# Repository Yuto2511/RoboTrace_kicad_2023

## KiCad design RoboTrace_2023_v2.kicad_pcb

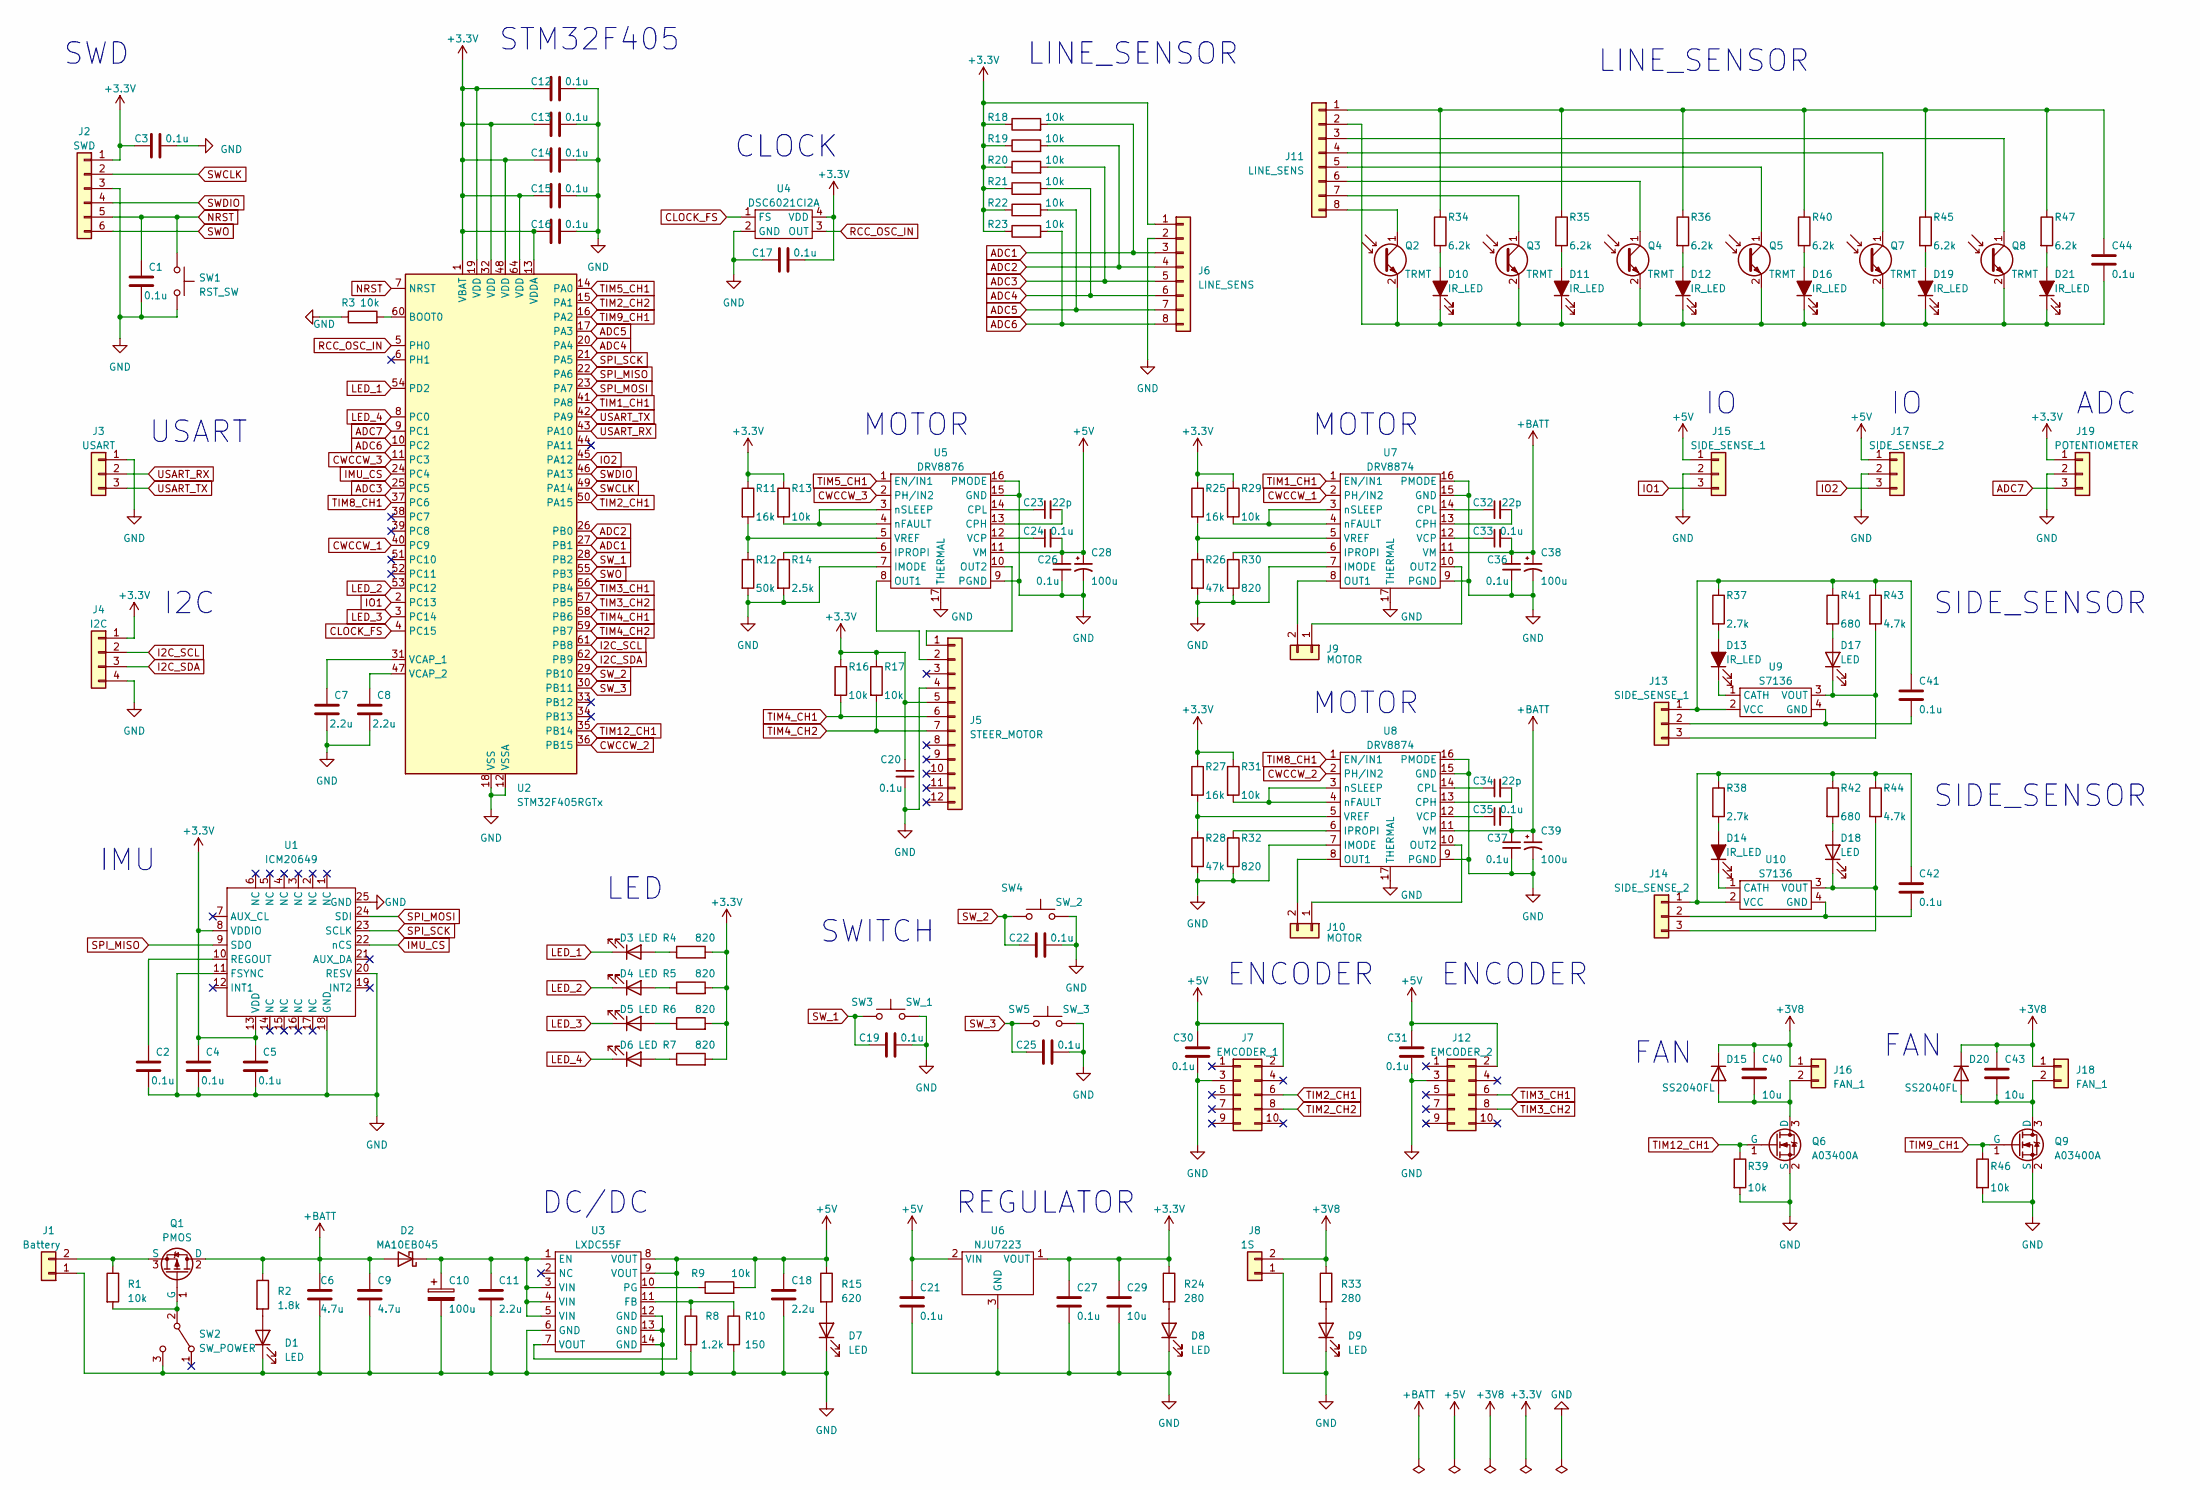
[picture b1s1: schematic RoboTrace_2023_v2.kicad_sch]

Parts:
C1, C2, C3, C4, C5, C12, C13, C14, C15, C16, C17, C19, C20, C21, C22, C24, C25, C26, C27, C30, C31, C33, C35, C36, C37, C41, C42, C44: 0.1u; C_0603_1608Metric
C6, C9: 4.7u; C_1206_3216Metric
C7, C8, C11, C18: 2.2u; C_0603_1608Metric
C10, C28, C38, C39: 100u; CP_EIA-7343-15_Kemet-W
C23, C32, C34: 22p; C_0603_1608Metric
C29, C40, C43: 10u; C_0805_2012Metric
D1, D3, D4, D5, D6, D7, D8, D9, D17, D18: LED; LED_0603_1608Metric
D2: MA10EB045; SO-221BC
D10, D11, D12, D13, D14, D16, D19, D21: IR_LED; LED_0603_1608Metric
D15, D20: SS2040FL; D_SOD-123F
J1: Battery; AMASS_XT30PW-M_1x02_P2.50mm_Horizontal
J2: SWD; JST_SH_BM06B-SRSS-TB_1x06-1MP_P1.00mm_Vertical
J3: USART; JST_SH_BM03B-SRSS-TB_1x03-1MP_P1.00mm_Vertical
J4: I2C; JST_SH_BM04B-SRSS-TB_1x04-1MP_P1.00mm_Vertical
J5: STEER_MOTOR; Molex_200528-0120_1x12-0.5MP_P0.50mm_Horizontal
J6, J11: LINE_SENS; Molex_200528-0080_1x08-0.5MP_P0.50mm_Horizontal
J7: EMCODER_1; PinHeader_2x05_P1.27mm_Vertical
J8: 1S; IL-G_2PIN
J9, J10: MOTOR; JST_PH_B2B-PH-K_1x02_P2.00mm_Vertical
J12: EMCODER_2; PinHeader_2x05_P1.27mm_Vertical
J13, J15: SIDE_SENSE_1; JST_SH_BM03B-SRSS-TB_1x03-1MP_P1.00mm_Vertical
J14, J17: SIDE_SENSE_2; JST_SH_BM03B-SRSS-TB_1x03-1MP_P1.00mm_Vertical
J16, J18: FAN_1; JST_PH_B2B-PH-K_1x02_P2.00mm_Vertical
J19: POTENTIOMETER; JST_SH_BM03B-SRSS-TB_1x03-1MP_P1.00mm_Vertical
Q1: PMOS; TO-252-3_TabPin2
Q2, Q3, Q4, Q5, Q7, Q8: TRMT; LED_0805_2012Metric
Q6, Q9: A03400A; SOT-23
R1, R3, R9, R13, R16, R17, R18, R19, R20, R21, R22, R23, R29, R31, R39, R46: 10k; R_0603_1608Metric
R2: 1.8k; R_0603_1608Metric
R4, R5, R6, R7, R30, R32: 820; R_0603_1608Metric
R8: 1.2k; R_0603_1608Metric
R10: 150; R_0603_1608Metric
R11, R25, R27: 16k; R_0603_1608Metric
R12: 50k; R_0603_1608Metric
R14: 2.5k; R_0603_1608Metric
R15: 620; R_0603_1608Metric
R24, R33: 280; R_0603_1608Metric
R26, R28: 47k; R_0603_1608Metric
R34, R35, R36, R40, R45, R47: 6.2k; R_0603_1608Metric
R37, R38: 2.7k; R_0603_1608Metric
R41, R42: 680; R_0603_1608Metric
R43, R44: 4.7k; R_0603_1608Metric
SW1: RST_SW; SW_SPST_B3U-1000P
SW2: SW_POWER; SSAJ12
SW3: SW_1; SW_SPST_B3U-1000P
SW4: SW_2; SW_SPST_B3U-1000P
SW5: SW_3; SW_SPST_B3U-1000P
U1: ICM20649; QFN-24-1EP_3x3mm_P0.4mm_EP1.75x1.6mm_ThermalVias
U2: STM32F405RGTx; LQFP-64_10x10mm_P0.5mm
U3: LXDC55F; LXDC55FAAA203
U4: DSC6021CI2A
U5: DRV8876; HTSSOP-16-1EP_4.4x5mm_P0.65mm_EP3.4x5mm_Mask2.46x2.31mm_The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
U6: NJU7223; TO-252-2
U7, U8: DRV8874; HTSSOP-16-1EP_4.4x5mm_P0.65mm_EP3.4x5mm_Mask2.46x2.31mm_The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
U9, U10: S7136

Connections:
+3.3V: C3.1, C4.1, C5.1, C12.1, C13.1, C14.1, C15.1, C16.1, C17.2, C20.1, C27.1, C29.1, J2.1, J4.1, J5.5, J6.1, J19.1, R4.2, R5.2, R6.2, R7.2, R11.1, R13.1, R16.1, R17.1, R18.1, R19.1, R20.1, R21.1, R22.1, R23.1, R24.1, R25.1, R27.1, R29.1, R31.1, U1.8 (VDDIO), U1.13 (VDD), U2.1 (VBAT), U2.13 (VDDA), U2.19 (VDD), U2.32 (VDD), U2.48 (VDD), U2.64 (VDD), U4.4 (VDD), U6.1 (VOUT)
+3V8: C40.1, C43.1, D15.1 (K), D20.1 (K), J8.2, J16.1, J18.1, R33.1
+5V: C18.1, C21.1, C24.2, C26.1, C28.1, C30.1, C31.1, J7.2, J12.2, J15.1, J17.1, R9.2, R15.1, U3.7 (VOUT), U3.8 (VOUT), U3.9 (VOUT), U5.11 (VM), U6.2 (VIN)
+BATT: C6.1, C9.1, C33.2, C35.2, C36.1, C37.1, C38.1, C39.1, D2.2 (A), Q1.2 (D), R2.1, U7.11 (VM), U8.11 (VM)
ADC1: J6.3, R18.2, U2.27 (PB1)
ADC2: J6.4, R19.2, U2.26 (PB0)
ADC3: J6.5, R20.2, U2.25 (PC5)
ADC4: J6.6, R21.2, U2.20 (PA4)
ADC5: J6.7, R22.2, U2.17 (PA3)
ADC6: J6.8, R23.2, U2.10 (PC2)
ADC7: J19.3, U2.9 (PC1)
CLOCK_FS: U2.4 (PC15), U4.1 (FS)
CWCCW_1: U2.40 (PC9), U7.2 (PH/IN2)
CWCCW_2: U2.36 (PB15), U8.2 (PH/IN2)
CWCCW_3: U2.11 (PC3), U5.2 (PH/IN2)
GND: C1.2, C2.2, C3.2, C4.2, C5.2, C6.2, C7.2, C8.2, C9.2, C10.2, C11.2, C12.2, C13.2, C14.2, C15.2, C16.2, C17.1, C18.2, C19.2, C20.2, C21.2, C22.2, C25.2, C26.2, C27.2, C28.2, C29.2, C30.2, C31.2, C36.2, C37.2, C38.2, C39.2, D1.1 (K), D7.1 (K), D8.1 (K), D9.1 (K), J1.1, J2.3, J3.1, J4.4, J5.4, J6.2, J7.3, J8.1, J12.3, J15.2, J17.2, J19.2, Q6.2 (S), Q9.2 (S), R3.1, R8.2, R10.2, R12.2, R14.2, R26.2, R28.2, R30.2, R32.2, R39.2, R46.2, SW1.2, SW2.3 (C), SW3.2, SW4.2, SW5.2, U1.11 (FSYNC), U1.18 (GND), U1.20 (RESV), U1.25 (GND), U2.12 (VSSA), U2.18 (VSS), U2.63 (VSS), U3.6 (GND), U3.12 (GND), U3.13 (GND), U3.14 (GND), U4.2 (GND), U5.7 (IMODE), U5.9 (PGND), U5.15 (GND), U5.16 (PMODE), U5.17 (THERMAL), U6.3 (GND), U7.7 (IMODE), U7.9 (PGND), U7.15 (GND), U7.16 (PMODE), U7.17 (THERMAL), U8.7 (IMODE), U8.9 (PGND), U8.15 (GND), U8.16 (PMODE), U8.17 (THERMAL)
I2C_SCL: J4.2, U2.61 (PB8)
I2C_SDA: J4.3, U2.62 (PB9)
IMU_CS: U1.22 (nCS), U2.24 (PC4)
IO1: J15.3, U2.2 (PC13)
IO2: J17.3, U2.45 (PA12)
LED_1: D3.1 (K), U2.54 (PD2)
LED_2: D4.1 (K), U2.53 (PC12)
LED_3: D5.1 (K), U2.3 (PC14)
LED_4: D6.1 (K), U2.8 (PC0)
NRST: C1.1, J2.5, SW1.1, U2.7 (NRST)
unnamed: D1.2 (A), R2.2
unnamed: C10.1, C11.1, D2.1 (K), U3.1 (EN), U3.3 (VIN), U3.4 (VIN), U3.5 (VIN)
unnamed: D3.2 (A), R4.1
unnamed: D4.2 (A), R5.1
unnamed: D5.2 (A), R6.1
unnamed: D6.2 (A), R7.1
unnamed: D7.2 (A), R15.2
unnamed: D8.2 (A), R24.2
unnamed: D9.2 (A), R33.2
unnamed: D10.2 (A), R34.2
unnamed: C44.2, D10.1 (K), D11.1 (K), D12.1 (K), D16.1 (K), D19.1 (K), D21.1 (K), J11.2, Q2.2 (E), Q3.2 (E), Q4.2 (E), Q5.2 (E), Q7.2 (E), Q8.2 (E)
unnamed: D11.2 (A), R35.2
unnamed: D12.2 (A), R36.2
unnamed: D13.2 (A), R37.2
unnamed: D13.1 (K), U9.1 (CATH)
unnamed: D14.2 (A), R38.2
unnamed: D14.1 (K), U10.1 (CATH)
unnamed: C40.2, D15.2 (A), J16.2, Q6.3 (D)
unnamed: D16.2 (A), R40.2
unnamed: D17.2 (A), R41.2
unnamed: D17.1 (K), J13.3, R43.2, U9.3 (VOUT)
unnamed: D18.2 (A), R42.2
unnamed: D18.1 (K), J14.3, R44.2, U10.3 (VOUT)
unnamed: D19.2 (A), R45.2
unnamed: C43.2, D20.2 (A), J18.2, Q9.3 (D)
unnamed: D21.2 (A), R47.2
unnamed: J1.2, Q1.3 (S), R1.1
unnamed: J5.1, U5.10 (OUT2)
unnamed: J5.2, U5.8 (OUT1)
unnamed: J9.1, U7.10 (OUT2)
unnamed: J9.2, U7.8 (OUT1)
unnamed: J10.1, U8.10 (OUT2)
unnamed: J10.2, U8.8 (OUT1)
unnamed: C44.1, J11.1, R34.1, R35.1, R36.1, R40.1, R45.1, R47.1
unnamed: J11.3, Q8.1 (C)
unnamed: J11.4, Q7.1 (C)
unnamed: J11.5, Q5.1 (C)
unnamed: J11.6, Q4.1 (C)
unnamed: J11.7, Q3.1 (C)
unnamed: J11.8, Q2.1 (C)
unnamed: C41.1, J13.1, R37.1, R41.1, R43.1, U9.2 (VCC)
unnamed: C41.2, J13.2, U9.4 (GND)
unnamed: C42.1, J14.1, R38.1, R42.1, R44.1, U10.2 (VCC)
unnamed: C42.2, J14.2, U10.4 (GND)
unnamed: Q1.1 (G), R1.2, SW2.2 (B)
unnamed: C2.1, U1.10 (REGOUT)
unnamed: R3.2, U2.60 (BOOT0)
unnamed: C7.1, U2.31 (VCAP_1)
unnamed: C8.1, U2.47 (VCAP_2)
unnamed: R8.1, R10.1, U3.11 (FB)
unnamed: R9.1, U3.10 (PG)
unnamed: C23.2, U5.13 (CPH)
unnamed: C23.1, U5.14 (CPL)
unnamed: R14.1, U5.6 (IPROPI)
unnamed: C24.1, U5.12 (VCP)
unnamed: R11.2, R12.1, U5.5 (VREF)
unnamed: R13.2, U5.3 (nSLEEP), U5.4 (nFAULT)
unnamed: C32.2, U7.13 (CPH)
unnamed: C32.1, U7.14 (CPL)
unnamed: R30.1, U7.6 (IPROPI)
unnamed: C33.1, U7.12 (VCP)
unnamed: R25.2, R26.1, U7.5 (VREF)
unnamed: R29.2, U7.3 (nSLEEP), U7.4 (nFAULT)
unnamed: C34.2, U8.13 (CPH)
unnamed: C34.1, U8.14 (CPL)
unnamed: R32.1, U8.6 (IPROPI)
unnamed: C35.1, U8.12 (VCP)
unnamed: R27.2, R28.1, U8.5 (VREF)
unnamed: R31.2, U8.3 (nSLEEP), U8.4 (nFAULT)
RCC_OSC_IN: U2.5 (PH0), U4.3 (OUT)
SPI_MISO: U1.9 (SDO), U2.22 (PA6)
SPI_MOSI: U1.24 (SDI), U2.23 (PA7)
SPI_SCK: U1.23 (SCLK), U2.21 (PA5)
SWCLK: J2.2, U2.49 (PA14)
SWDIO: J2.4, U2.46 (PA13)
SWO: J2.6, U2.55 (PB3)
SW_1: C19.1, SW3.1, U2.28 (PB2)
SW_2: C22.1, SW4.1, U2.29 (PB10)
SW_3: C25.1, SW5.1, U2.30 (PB11)
TIM1_CH1: U2.41 (PA8), U7.1 (EN/IN1)
TIM2_CH1: J7.6, U2.50 (PA15)
TIM2_CH2: J7.8, U2.15 (PA1)
TIM3_CH1: J12.6, U2.56 (PB4)
TIM3_CH2: J12.8, U2.57 (PB5)
TIM4_CH1: J5.6, R16.2, U2.58 (PB6)
TIM4_CH2: J5.7, R17.2, U2.59 (PB7)
TIM5_CH1: U2.14 (PA0), U5.1 (EN/IN1)
TIM8_CH1: U2.37 (PC6), U8.1 (EN/IN1)
TIM9_CH1: Q9.1 (G), R46.1, U2.16 (PA2)
TIM12_CH1: Q6.1 (G), R39.1, U2.35 (PB14)
USART_RX: J3.2, U2.43 (PA10)
USART_TX: J3.3, U2.42 (PA9)

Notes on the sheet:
MOTOR
ENCODER
CLOCK
SWITCH
SIDE_SENSOR
REGULATOR
SWD
FAN
DC/DC
STM32F405
LINE_SENSOR
LED
ADC
USART
I2C
IMU

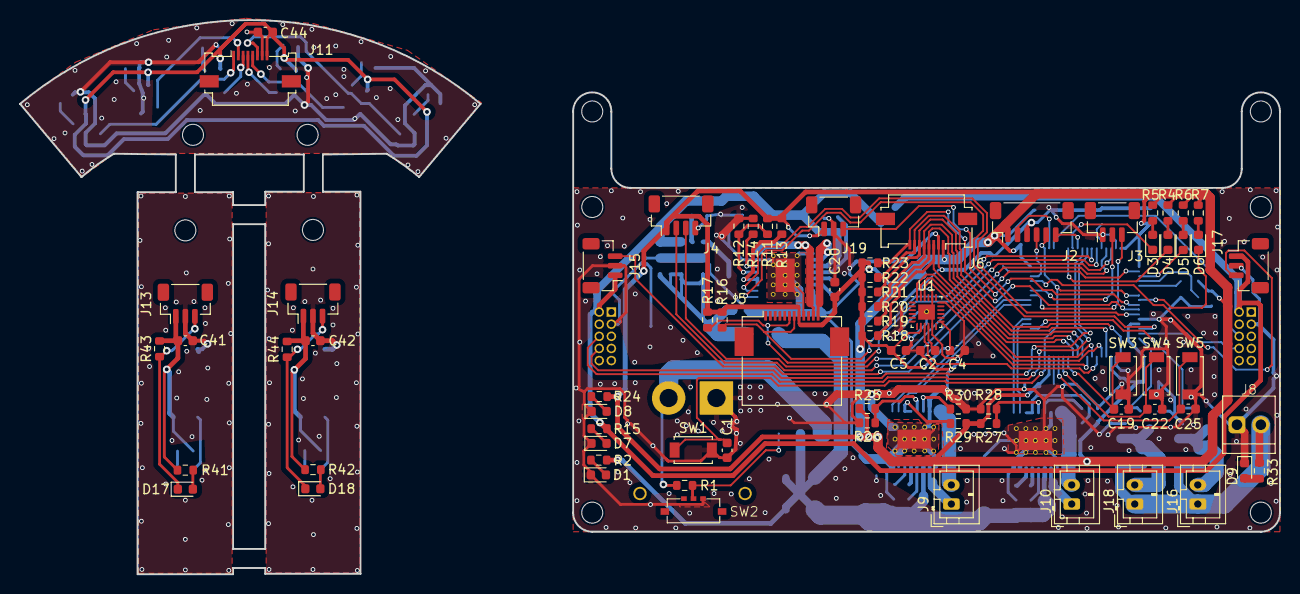
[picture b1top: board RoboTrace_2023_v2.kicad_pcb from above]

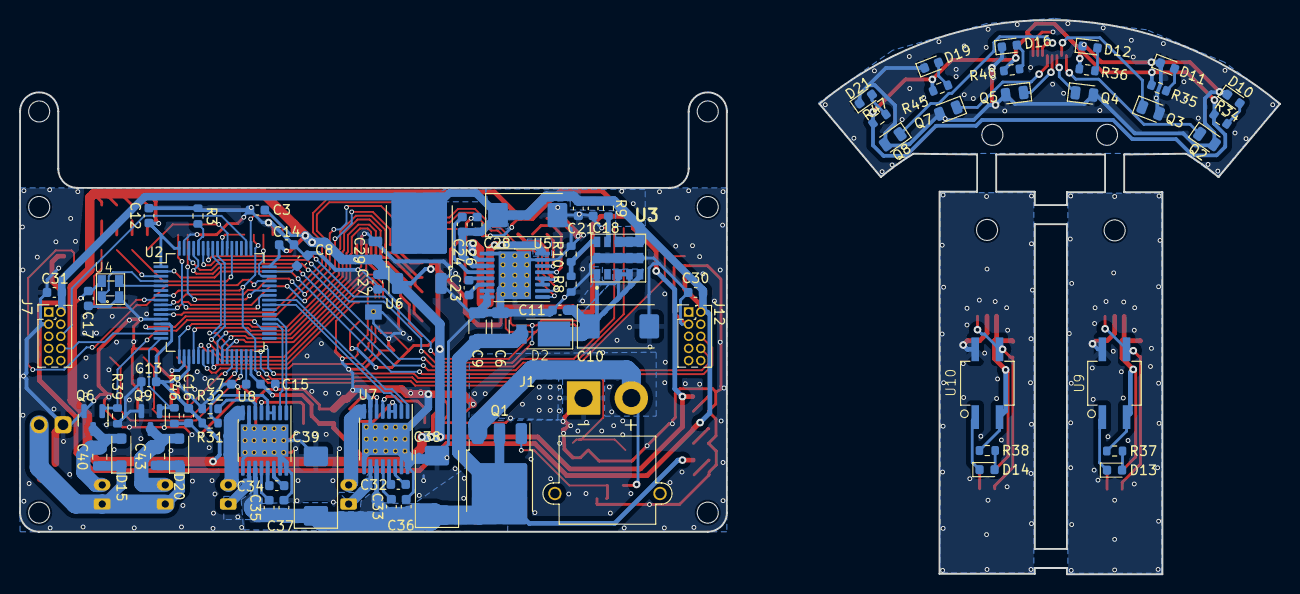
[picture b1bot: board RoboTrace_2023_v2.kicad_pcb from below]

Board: 2 copper layers, 131.9 x 58.0 mm, 155 parts (81 on the bottom side), 118 nets.

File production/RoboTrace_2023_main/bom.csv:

Designator,Footprint,Quantity,Value,LCSC Part #
"C1, C12, C13, C14, C15, C16, C17, C19, C2, C20, C21, C22, C24, C25, C26, C27, C3, C30, C31, C33, C35, C36, C37, C4, C5",0603,25,0.1u,
"C10, C28, C38, C39",CP_EIA-7343-15_Kemet-W,4,100u,
"C11, C18, C7, C8",0603,4,2.2u,
"C23, C32, C34",0603,3,22p,
"C29, C40, C43",0805,3,10u,
"C6, C9",1206,2,4.7u,
"D1, D3, D4, D5, D6, D7, D8, D9",0603,8,LED,
"D15, D20",D_SOD-123F,2,SS2040FL,
D2,SO-221BC,1,MA10EB045,
J1,AMASS_XT30PW-M_1x02_P2.50mm_Horizontal,1,Battery,
"J10, J9",JST_PH_B2B-PH-K_1x02_P2.00mm_Vertical,2,MOTOR,
J12,PinHeader_2x05_P1.27mm_Vertical,1,EMCODER_2,
J15,JST_SH_BM03B-SRSS-TB_1x03-1MP_P1.00mm_Vertical,1,SIDE_SENSE_1,
"J16, J18",JST_PH_B2B-PH-K_1x02_P2.00mm_Vertical,2,FAN_1,
J17,JST_SH_BM03B-SRSS-TB_1x03-1MP_P1.00mm_Vertical,1,SIDE_SENSE_2,
J19,JST_SH_BM03B-SRSS-TB_1x03-1MP_P1.00mm_Vertical,1,POTENTIOMETER,
J2,JST_SH_BM06B-SRSS-TB_1x06-1MP_P1.00mm_Vertical,1,SWD,
J3,JST_SH_BM03B-SRSS-TB_1x03-1MP_P1.00mm_Vertical,1,USART,
J4,JST_SH_BM04B-SRSS-TB_1x04-1MP_P1.00mm_Vertical,1,I2C,
J5,Molex_200528-0120_1x12-0.5MP_P0.50mm_Horizontal,1,STEER_MOTOR,
J6,Molex_200528-0080_1x08-0.5MP_P0.50mm_Horizontal,1,LINE_SENS,
J7,PinHeader_2x05_P1.27mm_Vertical,1,EMCODER_1,
J8,IL-G_2PIN,1,1S,
Q1,TO-252-3_TabPin2,1,PMOS,
"Q6, Q9",SOT-23,2,A03400A,
"R1, R13, R16, R17, R18, R19, R20, R21, R22, R23, R29, R3, R31, R39, R46, R9",0603,16,10k,
R10,0603,1,150,
"R11, R25, R27",0603,3,16k,
R12,0603,1,50k,
R14,0603,1,2.5k,
R15,0603,1,620,
R2,0603,1,1.8k,
"R24, R33",0603,2,280,
"R26, R28",0603,2,47k,
"R30, R32, R4, R5, R6, R7",0603,6,820,
R8,0603,1,1.2k,
SW1,SW_SPST_B3U-1000P,1,RST_SW,
SW2,SSAJ12,1,SW_POWER,
SW3,SW_SPST_B3U-1000P,1,SW_1,
SW4,SW_SPST_B3U-1000P,1,SW_2,
SW5,SW_SPST_B3U-1000P,1,SW_3,
U1,QFN-24-1EP_3x3mm_P0.4mm_EP1.75x1.6mm_ThermalVias,1,ICM20649,
U2,LQFP-64_10x10mm_P0.5mm,1,STM32F405RGTx,
U3,LXDC55FAAA203,1,LXDC55F,
U4,DSC6021CI2A,1,DSC6021CI2A,
U5,HTSSOP-16-1EP_4.4x5mm_P0.65mm_EP3.4x5mm_Mask2.46x2.31mm_ThermalVias,1,DRV8876,
U6,TO-252-2,1,NJU7223,
"U7, U8",HTSSOP-16-1EP_4.4x5mm_P0.65mm_EP3.4x5mm_Mask2.46x2.31mm_ThermalVias,2,DRV8874,

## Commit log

2024-01-15 second commit
2024-01-17 third commit
2024-01-17 add production
